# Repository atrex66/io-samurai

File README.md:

# io-samurai
An open-source, budget-friendly CNC Input Output interface for LinuxCNC, 16 inputs (20–50 V), 8 high-current outputs (50 V, 500 mA Max), and single analog input (0–3.3 V). Supports W5100S-EVB-Pico module. Further support W5500-lite + pico or pico2

## Features
- **High-Speed Interface**: W5100S-evb-pico Ethernet. https://docs.wiznet.io/Product/iEthernet/W5100S/w5100s-evb-pico
- **Inputs**: 16 channels (MCP23017, I2C), 20–50 V, with 10 kΩ/1.5 kΩ divider and 3.6 V Zener protection.
- **Outputs**: 8 channels (TD62783 Darlington driver, MCP23008-controlled), 50 V, 500 mA/channel.
- **Analog Inputs**: 1 channels (GP26), 12-bit, ~10 kΩ potentiometer, 100 nF filtering.
- **Display**: Optional SH1106 OLED (128x64) for I/O status and IP address (not required for operation).
- **Software**:
  - LinuxCNC HAL driver, with safety functions (timeout, data checks).
  - Python library for automation/remote I/O.
  - Further Mach3 driver development.
- **Hardware Support**: W5100S-EVB-Pico.
- **Open-Source**: All code, PCB production files, and docs under MIT License.

## Support
- **Notes**: If you want to buy ready to go io-samurai send message to me for options.
- **Patreon**: Join our community at [patreon](https://www.patreon.com/c/user?u=43314769).

## License
This project is licensed under the MIT License. See [LICENSE](LICENSE).
The `ioLibrary_Driver` in `firmware/pico/ioLibrary_Driver.zip` is licensed under the MIT License by Wiznet. See [firmware/pico/ioLibrary_Driver.zip/LICENSE.txt](firmware/pico/ioLibrary_Driver.zip/LICENSE.txt).

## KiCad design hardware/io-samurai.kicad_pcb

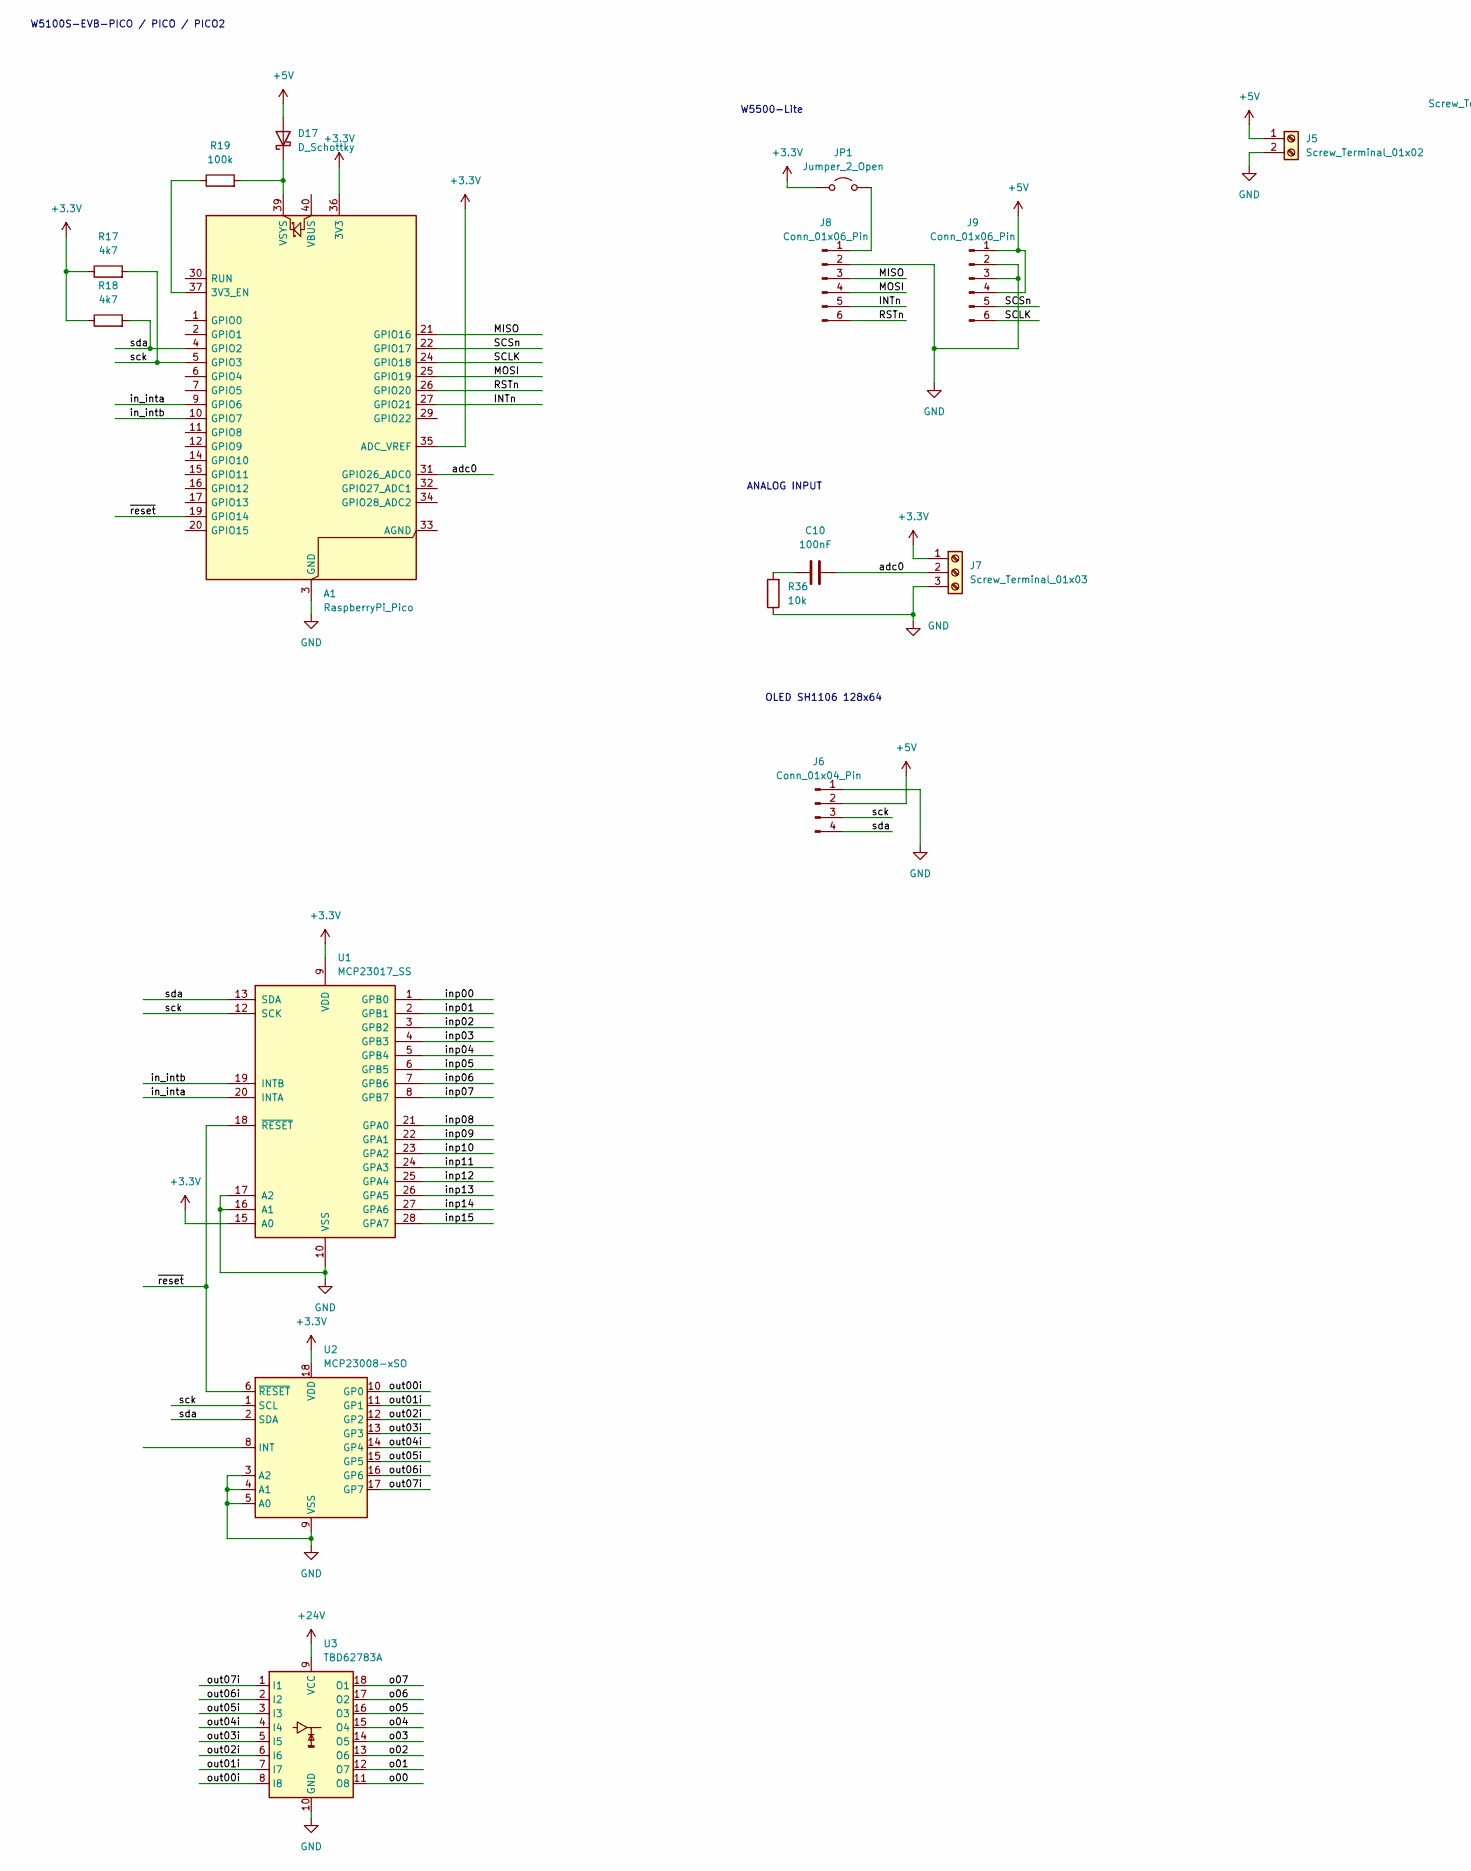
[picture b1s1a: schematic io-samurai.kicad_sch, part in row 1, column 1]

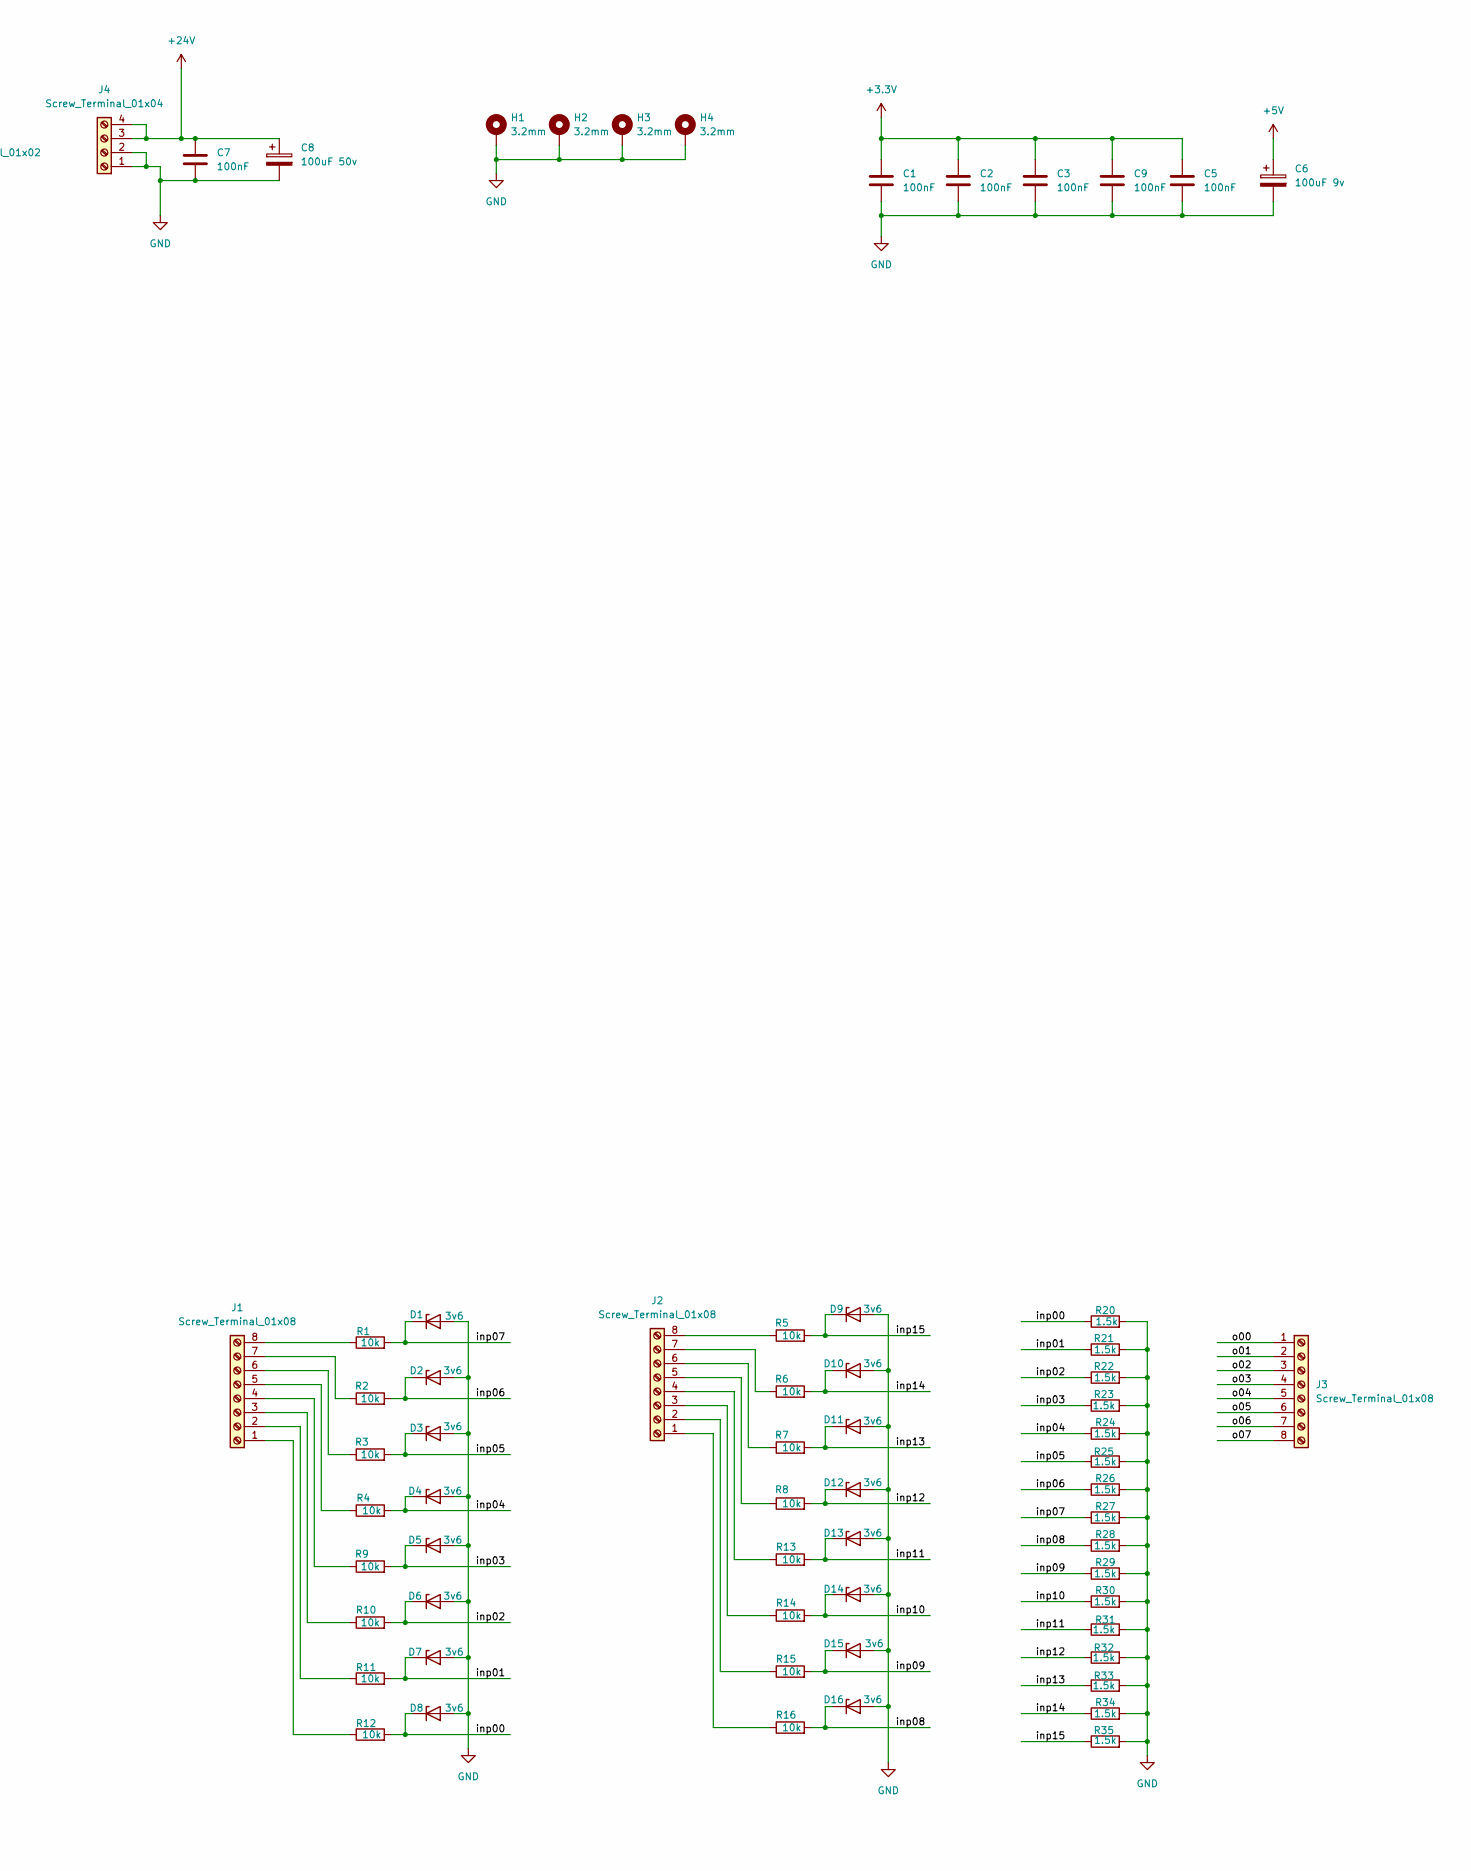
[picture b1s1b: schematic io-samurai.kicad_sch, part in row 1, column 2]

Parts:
A1: RaspberryPi_Pico; RaspberryPi_Pico_Common_THT
C1, C2, C3, C5, C7, C9, C10: 100nF; C_1206_3216Metric
C6: 100uF 9v; CP_Elec_8x5.4
C8: 100uF 50v; CP_Elec_8x5.4
D1, D2, D3, D4, D5, D6, D7, D8, D9, D10, D11, D12, D13, D14, D15, D16: 3v6; D_SOD-523
D17: D_Schottky; D_SOD-523
H1, H2, H3, H4: 3.2mm; MountingHole_3.2mm_M3_Pad_TopBottom
J1, J2, J3: Screw_Terminal_01x08; TerminalBlock_Xinya_XY308-2.54-8P_1x08_P2.54mm_Horizontal
J4: Screw_Terminal_01x04; TerminalBlock_Xinya_XY308-2.54-4P_1x04_P2.54mm_Horizontal
J5: Screw_Terminal_01x02; TerminalBlock_Xinya_XY308-2.54-2P_1x02_P2.54mm_Horizontal
J6: Conn_01x04_Pin; PinHeader_1x04_P2.54mm_Vertical
J7: Screw_Terminal_01x03; TerminalBlock_Xinya_XY308-2.54-3P_1x03_P2.54mm_Horizontal
J8, J9: Conn_01x06_Pin; PinHeader_1x06_P2.54mm_Vertical
JP1: Jumper_2_Open; SolderJumper-2_P1.3mm_Open_TrianglePad1.0x1.5mm
R1, R2, R3, R4, R5, R6, R7, R8, R9, R10, R11, R12, R13, R14, R15, R16, R36: 10k; R_0805_2012Metric
R17, R18: 4k7; R_0805_2012Metric
R19: 100k; R_0805_2012Metric
R20, R21, R22, R23, R24, R25, R26, R27, R28, R29, R30, R31, R32, R33, R34, R35: 1.5k; R_0805_2012Metric
U1: MCP23017_SS; SSOP-28_5.3x10.2mm_P0.65mm
U2: MCP23008-xSO; SOIC-18W_7.5x11.6mm_P1.27mm
U3: TBD62783A; SOIC-18W_7.5x11.6mm_P1.27mm

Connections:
+3.3V: A1.35 (ADC_VREF), A1.36 (3V3), C1.1, C2.1, C3.1, C5.1, C9.1, J7.1, JP1.1 (A), R17.1, R18.1, U1.9 (VDD), U1.15 (A0), U2.18 (VDD)
+5V: C6.1, D17.2 (A), J5.1, J6.2, J9.1, J9.4
+24V: C7.1, C8.1, J4.3, J4.4, U3.9 (VCC)
/INTn: A1.27 (GPIO21), J8.5
/MISO: A1.21 (GPIO16), J8.3
/MOSI: A1.25 (GPIO19), J8.4
/RSTn: A1.26 (GPIO20), J8.6
/SCLK: A1.24 (GPIO18), J9.6
/SCSn: A1.22 (GPIO17), J9.5
/adc0: A1.31 (GPIO26_ADC0), C10.1, J7.2
/in_inta: A1.9 (GPIO6), U1.20 (INTA)
/in_intb: A1.10 (GPIO7), U1.19 (INTB)
/inp00: D8.1 (K), R12.2, R20.1, U1.1 (GPB0)
/inp01: D7.1 (K), R11.2, R21.1, U1.2 (GPB1)
/inp02: D6.1 (K), R10.2, R22.1, U1.3 (GPB2)
/inp03: D5.1 (K), R9.2, R23.1, U1.4 (GPB3)
/inp04: D4.1 (K), R4.2, R24.1, U1.5 (GPB4)
/inp05: D3.1 (K), R3.2, R25.1, U1.6 (GPB5)
/inp06: D2.1 (K), R2.2, R26.1, U1.7 (GPB6)
/inp07: D1.1 (K), R1.2, R27.1, U1.8 (GPB7)
/inp08: D16.1 (K), R16.2, R28.1, U1.21 (GPA0)
/inp09: D15.1 (K), R15.2, R29.1, U1.22 (GPA1)
/inp10: D14.1 (K), R14.2, R30.1, U1.23 (GPA2)
/inp11: D13.1 (K), R13.2, R31.1, U1.24 (GPA3)
/inp12: D12.1 (K), R8.2, R32.1, U1.25 (GPA4)
/inp13: D11.1 (K), R7.2, R33.1, U1.26 (GPA5)
/inp14: D10.1 (K), R6.2, R34.1, U1.27 (GPA6)
/inp15: D9.1 (K), R5.2, R35.1, U1.28 (GPA7)
/o00: J3.1, U3.11 (O8)
/o01: J3.2, U3.12 (O7)
/o02: J3.3, U3.13 (O6)
/o03: J3.4, U3.14 (O5)
/o04: J3.5, U3.15 (O4)
/o05: J3.6, U3.16 (O3)
/o06: J3.7, U3.17 (O2)
/o07: J3.8, U3.18 (O1)
/out00i: U2.10 (GP0), U3.8 (I8)
/out01i: U2.11 (GP1), U3.7 (I7)
/out02i: U2.12 (GP2), U3.6 (I6)
/out03i: U2.13 (GP3), U3.5 (I5)
/out04i: U2.14 (GP4), U3.4 (I4)
/out05i: U2.15 (GP5), U3.3 (I3)
/out06i: U2.16 (GP6), U3.2 (I2)
/out07i: U2.17 (GP7), U3.1 (I1)
/sck: A1.5 (GPIO3), J6.3, R17.2, U1.12 (SCK), U2.1 (SCL)
/sda: A1.4 (GPIO2), J6.4, R18.2, U1.13 (SDA), U2.2 (SDA)
/~reset: A1.19 (GPIO14), U1.18 (~RESET), U2.6 (~RESET)
GND: A1.3 (GND), A1.8 (GND), A1.13 (GND), A1.18 (GND), A1.23 (GND), A1.28 (GND), A1.38 (GND), C1.2, C2.2, C3.2, C5.2, C6.2, C7.2, C8.2, C9.2, D1.2 (A), D2.2 (A), D3.2 (A), D4.2 (A), D5.2 (A), D6.2 (A), D7.2 (A), D8.2 (A), D9.2 (A), D10.2 (A), D11.2 (A), D12.2 (A), D13.2 (A), D14.2 (A), D15.2 (A), D16.2 (A), H1.1, H2.1, H3.1, H4.1, J4.1, J4.2, J5.2, J6.1, J7.3, J8.2, J9.2, J9.3, R20.2, R21.2, R22.2, R23.2, R24.2, R25.2, R26.2, R27.2, R28.2, R29.2, R30.2, R31.2, R32.2, R33.2, R34.2, R35.2, R36.1, U1.10 (VSS), U1.16 (A1), U1.17 (A2), U2.3 (A2), U2.4 (A1), U2.5 (A0), U2.9 (VSS), U3.10 (GND)
unnamed: A1.37 (3V3_EN), R19.1
unnamed: A1.39 (VSYS), D17.1 (K), R19.2
unnamed: C10.2, R36.2
unnamed: J1.1, R12.1
unnamed: J1.2, R11.1
unnamed: J1.3, R10.1
unnamed: J1.4, R9.1
unnamed: J1.5, R4.1
unnamed: J1.6, R3.1
unnamed: J1.7, R2.1
unnamed: J1.8, R1.1
unnamed: J2.1, R16.1
unnamed: J2.2, R15.1
unnamed: J2.3, R14.1
unnamed: J2.4, R13.1
unnamed: J2.5, R8.1
unnamed: J2.6, R7.1
unnamed: J2.7, R6.1
unnamed: J2.8, R5.1
unnamed: J8.1, JP1.2 (B)

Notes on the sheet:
W5500-Lite
OLED SH1106 128x64
ANALOG INPUT
W5100S-EVB-PICO / PICO / PICO2

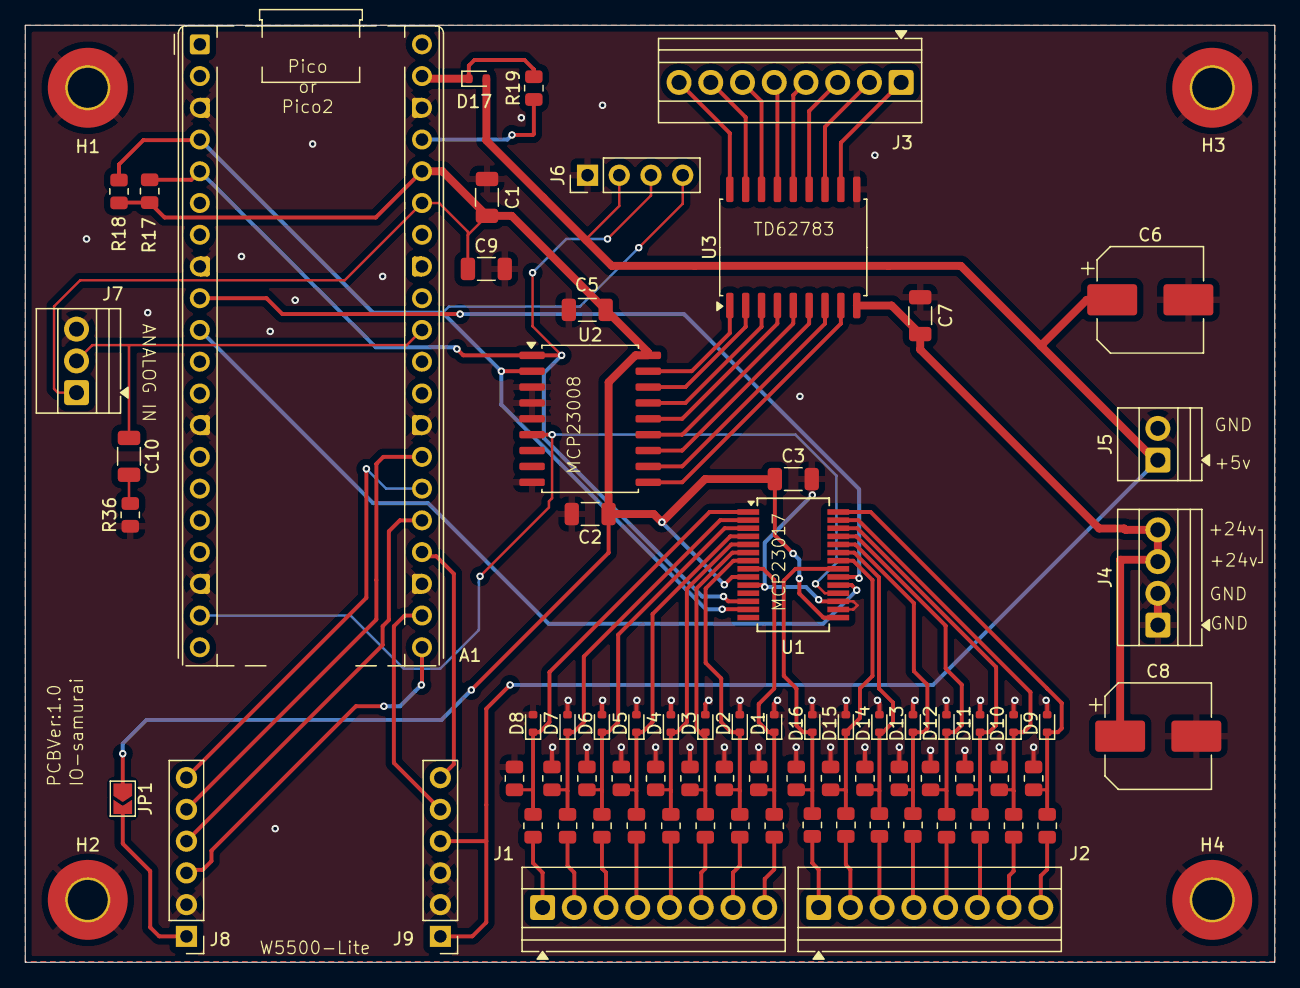
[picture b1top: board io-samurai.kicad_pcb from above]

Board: 2 copper layers, 100.0 x 75.0 mm, 80 parts (0 on the bottom side), 68 nets.

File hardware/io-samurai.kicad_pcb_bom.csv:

Designator,Quantity,Value,Footprint,Package,MPN,DNP,Mount_Type,Description
A1,1,RaspberryPi_Pico,RaspberryPi_Pico_Common_THT,,,,tht,"Versatile and inexpensive wireless microcontroller module powered by RP2040 dual-core Arm Cortex-M0+ processor up to 133 MHz, 264kB SRAM, 2MB QSPI flash, Infineon CYW43439 2.4GHz 802.11n wireless LAN; also supports Raspberry Pi Pico 2 W"
"C1, C10, C2, C3, C5, C7, C9",7,100nF,C_1206_3216Metric,,,,smt,Unpolarized capacitor
C6,1,100uF 9v,CP_Elec_8x5.4,,,,smt,Polarized capacitor
C8,1,100uF 50v,CP_Elec_8x5.4,,,,smt,Polarized capacitor
"D1, D10, D11, D12, D13, D14, D15, D16, D2, D3, D4, D5, D6, D7, D8, D9",16,3v6,D_SOD-523,,,,smt,Zener diode
D17,1,D_Schottky,D_SOD-523,,,,smt,Schottky diode
"J1, J2, J3",3,Screw_Terminal_01x08,TerminalBlock_Xinya_XY308-2.54-8P_1x08_P2.54mm_Horizontal,,,,tht,"Generic screw terminal, single row, 01x08, script generated (kicad-library-utils/schlib/autogen/connector/)"
J4,1,Screw_Terminal_01x04,TerminalBlock_Xinya_XY308-2.54-4P_1x04_P2.54mm_Horizontal,,,,tht,"Generic screw terminal, single row, 01x04, script generated (kicad-library-utils/schlib/autogen/connector/)"
J5,1,Screw_Terminal_01x02,TerminalBlock_Xinya_XY308-2.54-2P_1x02_P2.54mm_Horizontal,,,,tht,"Generic screw terminal, single row, 01x02, script generated (kicad-library-utils/schlib/autogen/connector/)"
J6,1,Conn_01x04_Pin,PinHeader_1x04_P2.54mm_Vertical,,,,tht,"Generic connector, single row, 01x04, script generated"
J7,1,Screw_Terminal_01x03,TerminalBlock_Xinya_XY308-2.54-3P_1x03_P2.54mm_Horizontal,,,,tht,"Generic screw terminal, single row, 01x03, script generated (kicad-library-utils/schlib/autogen/connector/)"
"J8, J9",2,Conn_01x06_Pin,PinHeader_1x06_P2.54mm_Vertical,,,,tht,"Generic connector, single row, 01x06, script generated"
JP1,1,Jumper_2_Open,SolderJumper-2_P1.3mm_Open_TrianglePad1.0x1.5mm,,,,tht,"Jumper, 2-pole, open"
"R1, R10, R11, R12, R13, R14, R15, R16, R2, R3, R36, R4, R5, R6, R7, R8, R9",17,10k,R_0805_2012Metric,,,,smt,Resistor
"R17, R18",2,4k7,R_0805_2012Metric,,,,smt,Resistor
R19,1,100k,R_0805_2012Metric,,,,smt,Resistor
"R20, R21, R22, R23, R24, R25, R26, R27, R28, R29, R30, R31, R32, R33, R34, R35",16,1.5k,R_0805_2012Metric,,,,smt,Resistor
U1,1,MCP23017_SS,SSOP-28_5.3x10.2mm_P0.65mm,,,,smt,"16-bit I/O expander, I2C, interrupts, w pull-ups, SSOP-28"
U2,1,MCP23008-xSO,SOIC-18W_7.5x11.6mm_P1.27mm,,,,smt,"8-bit I/O expander, I2C, interrupts, SOIC-18"
U3,1,TBD62783A,SOIC-18W_7.5x11.6mm_P1.27mm,,,,smt,"8-Channel Source Type Transistor Array, TTL and CMOS compatible, 500mA, 50V, DIP-18/SOP-18/SSOP-18/SOIC-18W"

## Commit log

2025-04-17 Initial commit with io-samurai project files
2025-04-17 Update pinout.md with power requirements
2025-04-17 Update README.md with power requirements
2025-04-17 Changes to be committed: deleted: hardware/#auto_saved_files# deleted: hardware/fp-info-cache deleted: hardware/io-samurai-backups/io-samurai-2025-04-17_132557.zip deleted: hardware/io-samurai-backup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
2025-04-17 python library fixed, missing reset of output
2025-04-17 Hardware directory simplify
2025-04-17 hardware files for production added
2025-04-17 ioLibraryDriver compressed
2025-04-17 ioLibraryDriver directory excluded
2025-04-17 Adding user guide
2025-04-17 Adding user guide content
2025-04-17 hal file fix
2025-04-17 user manual changes
2025-04-17 added pinout.md
2025-04-17 updated ratings.md
2025-04-17 pico dir renamed to match hardware
2025-04-17 README.md fixed
2025-04-17 upload images
2025-04-17 removed mistaken personal image
2025-04-17 fixing text highlight
2025-04-17 .gitignore to reflect changes on firmware directory
2025-04-17 testing timeout change
2025-04-17 remove __pychache__
2025-04-18 __pycache__
2025-04-18 cmakelists.txt extreacts iolibrarydriver automaticly
2025-04-18 analog input added to pico and the hal driver
2025-04-18 automatic ioLibraryDriver extraction
2025-04-18 added analog rounding and converted to s32
2025-04-18 added not logic for Inputs
2025-04-18 io-ready-out disable when packet size mismatch
2025-04-18 Hal user guiide added
2025-04-18 Hal user guiide sample modified
2025-04-18 Hal user guiide invalid license corrected
2025-04-18 analog input handling added
2025-04-18 analog input test added
2025-04-19 switchable low pass filter added
2025-04-19 tuning of python driver
2025-04-19 Remove __pycache__ from git tracking
2025-04-19 added __pycache__ and python cache files to .gitignore
2025-04-19 python comments added
2025-04-19 further supported boards
2025-04-19 changed the order of drawing to lcd
2025-04-19 .c files moved to /src and CMakeLists.txt modified to reflect the changes
2025-04-19 terminal configuration separated from main.c
2025-04-19 changes made for serial terminal separation
2025-04-19 moved the font from the header file to the source
2025-04-19 remove comment
2025-04-19 added docs for hardware
2025-04-19 remove mistaken directories
2025-04-19 changes build configuration
2025-04-19 added lowpass filter switch for analog
2025-04-19 removed python benchmark mode
2025-04-19 docs not fit to MIT license changing to http links
2025-04-19 moving python tests to utility
2025-04-19 minimal example for multiple io-samurai
2025-04-19 io-samurai.py and jump_table.py changed to symbolic link to reduce redundancy
2025-04-19 symbolic link created for jump_table.py
2025-04-19 oled panel power changed to 3.3v
2025-04-19 ignore __pycache__ in utility and ignore compiled executable of benchmark
2025-04-19 added teardrops
2025-04-20 adding debug configuration for swd debugging
2025-04-21 checksum error cleared when timeout
2025-04-21 Added littlefs
2025-04-21 removed littlefs-project
2025-04-22 changed some features to reflect the project current state
2025-04-22 network configuration error fixed multiple io-samurai on the same network now working
2025-04-22 added dual analog test
2025-04-22 remove redundant network configuration
2025-04-22 adding multiple instance handling
2025-04-22 checksums for all instances separated
2025-04-23 fixed multiple instances shared memory variables
2025-04-23 change to Release build
2025-04-24 terminal config fixed and finished added bits to the transfer for hardware present detection
2025-04-24 changed to support hardware detection bits
2025-04-24 optimized use of variable (instances) removed num_entries
2025-04-24 added picture of the new v1.0 industrial pcb (3d model)
2025-04-24 2 new pins added, analog-min and analog-max instead of analog-scale
2025-04-24 benchmark fixed (only fix port worked 8888), variable for the port
2025-04-25 Multicore flash write fixed, using fifo to send command to core0 to wait for flash write
2025-04-26 Watchdog check added
2025-04-26 Changed flash write, added multicore_fifo_wready loop to the start of flash writing, to ensure write fifo is ready
2025-04-26 changed timeout handling position in the code to ensure nothing block the running especially the OLED code
2025-04-28 ignore local test files
2025-04-28 added function descriptions
2025-04-28 removed foreign language comments (hungary)
2025-04-28 nonrealtime cpp driver
2025-04-28 Readme.md added
2025-04-28 README.md corrected
2025-04-28 readme.md markup misplaces fix
2025-04-28 usage_example binary excluded
2025-04-29 wrong type of oled panel picture
2025-04-29 changed the example name from main.cpp to usage_example.cpp
2025-04-29 Added w5100s-ewb-pico link
2025-04-29 Added schematic in pdf
2025-04-29 io-samurai.pdf renamed io-samurai-sch.pdf
2025-05-16 fixed wrong variable set code
2025-06-04 changed the trace of the w5500 module
